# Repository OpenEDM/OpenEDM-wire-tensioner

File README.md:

# OpenEDM-wire-tensioner

This repository contains the design of the **Wire Tensioning Mechanism**, in particular, hardware design and firmware. Note that this design is a work in progress, it is not complete, and may contain errors.

Currently, the electronic hardware is assembled from heavily customized standard modules, as shown in the image below. An integrated hardware design is available in the [Hardware](https://github.com/OpenEDM/OpenEDM-wire-tensioner/tree/main/Hardware) directory, but it is still in the early stages of development.

The mechanical design of the wire tensioner is available as a part of the [OpenEDM-wire-machine design](https://github.com/OpenEDM/OpenEDM-wire-machine).

## Main design requirements

The wire tensioning mechanism must fulfill two main tasks:

1. Ensure that the wire in the cutting zone is fed according to the speed setpoint set by the user.
2. Ensure that the wire in the cutting zone is tensioned according to the tension setpoint set by the user.

## Operation principle

First, this is how the wire runs. On the right side (not shown in the photo) is the wire source; for example, a spool with new wire. On the left side (also not shown in the photo) is the location where the used wire is directed. This could be a spool for collecting the used wire, or a mechanism that cuts the wire into small pieces for convenient disposal:

Next, let's take a look at the wire tensioner's main components:

The wire enters the system through the **input wire feeder** (1). Then it passes around several passive pulleys. Next, the wire goes through the **wire guides** (6, 5). The **wire contacts** (7, 4), located near the wire guides, supply electricity to the wire. After that, the wire wraps around the last passive pulley, which is a part of the **load cell assembly** (10). Finally, the wire exits the system through the **output wire feeder** (8). All components are mounted on a frame, which consists of an **aluminum part** (2) and a **plastic part** (3). The system is controlled by an **electronic control unit** (9).

The system operates in such a way that the output feeder pulls the wire, while the input feeder, when necessary, slows the wire's movement by acting as a brake. The operation of the motors depends on the setpoints for speed and tension, as well as on the feedback signal from the load cell. More details are provided below.

There is an important design constraint for the input feeder: it must not deform the wire in any way, meaning it must not alter the shape of wire's cross-section. This constraint does not apply to the output feeder.

### Input wire feeder

To understand how this feeder works, let's look at how the wire is loaded into it. The wire enters the feeder through a PTFE tube connected to the **input fitting** (1.2). About one meter of wire should be pulled out from the tube, then placed into the groove of the **input latch** (1.1), and the latch should be closed. Next, the wire should be wrapped 4–5 times clockwise around the **pulley** (1.3). It doesn't matter if the loops are placed randomly; during operation, the feeder will self-correct their position. After that, without releasing the tension on the wire, the wire should be placed into the groove of the **output latch** (1.4) and the latch should be closed.

Some important points:
1. This feeder operates based on the [capstan effect](https://en.wikipedia.org/wiki/Capstan_equation).
1. For the feeder to operate correctly, the motor must rotate only clockwise, and there must always be some tension in the wire after the output latch.
1. Regarding the latches: the input and output latches are structurally identical. The input latch is shown in the closed position in the picture above, while the output latch is shown open. A closed latch significantly hinders the wire from passing through but does not block its movement completely.

### Output wire feeder

In this feeder, the main components are the pulleys, between which the wire is clamped. **Active puley** (8.6) is mounted directly on the motor shaft. **Passive puley** (8.7) is mounted on the **lever** (8.1) which rotates around the **axis** (8.3). Both pulleys have toothed rims that provide a kinematic connection between them. A **spring** (8.4), which presses against the **stop** (8.5), applies force to the lever, pushing the pulleys together and ensuring that the wire clamped between them cannot slip.

Again, let’s look at how the wire is loaded into this feeder. First, the lever (8.1) must be pressed to create a gap between pulleys (8.6) and (8.7). Then, the wire should be inserted into the hole marked with a red arrow. After that, the wire should pass between the pulleys and exit through the **output fitting** (8.2). Finally, the lever should be released so that the wire is clamped between the pulleys.

The main feature of this design is the construction of the pulleys. The pulleys must meet the following key requirements:

1. The surface that comes into contact with the wire must be hard enough so that the wire does not leave marks or cause deformation.
1. The pulleys must have an integrated toothed rim.

If the pulleys were made entirely of metal, manufacturing them would be a complex and costly task. However, a workaround was found that significantly simplifies the situation and reduces the cost. Each pulley is an assembly of three components:

1. An **outer bushing** (8.6.3) and an **inner bushing** (8.6.1). These bushings must be made of steel. However, due to their simple geometry, they can easily be sourced as off-the-shelf parts.
1. An **intermediate bushing** (8.6.2) with an integrated toothed rim. This bushing can simply be 3D-printed from a sufficiently strong plastic, such as ABS.

All three bushings -- outer, inner, and intermediate -- are press-fitted into one another. Of course, the dimensions of the plastic bushing must be chosen carefully to ensure a tight fit. This solution has been tested and has proven to work reliably in practice.

Another interesting aspect is the placement of the spring. It is easy to notice that the design of this feeder resembles that of a standard 3D printer extruder, for example, like [this one](https://youtu.be/zdTyMRBLIl4?t=35). However, in a typical 3D printer extruder, the spring is usually located inside, between the levers. In this design, the spring is placed on the outside.

The reason for this is that, for the feeder to work reliably, the pulleys axes must remain parallel, even when the spring applies significant pressure to the moving lever. Experiments have shown that the design with an externally mounted spring performs better in this regard.

### Load cell assembly

There is nothing particularly special about this part of the design. The **load cell** (10.2) is mounted on the wire tensioner frame using a **plastic holder** (10.1). The **passive pulley** (10.3) is attached to the load cell via another **plastic holder** (10.4).

The only noteworthy detail here is that the cable connecting the load cell to the electronic control unit is shielded, and the shield is electrically connected to the load cell beam. Often, the load cell beam is made of anodized aluminum, which prevents proper electrical contact; therefore, the anodized layer must be locally removed before connecting the cable shield to the beam.

### Control system operation algorithm

The current firmware version is located in the [corresponding folder](https://github.com/OpenEDM/OpenEDM-wire-tensioner/tree/main/Firmware). Below is a brief description of how it works:

Immediately after power is applied, the device performs a tare operation on the load cell. At this point, it is assumed that the wire is already loaded into the system. The input motor does not rotate. The output motor rotates in reverse to reduce the wire tension in the system. This reverse motion continues until the reading from the load cell stops changing. After that, the load cell is tared, and the device enters normal operation mode.

During normal operation, the following occurs:

1. The speed of the input motor depends only on the wire feed rate setpoint.
1. The speed of the output motor is controlled by a PID regulator, which receives the tension error as input -- that is, the difference between the actual tension (measured by the load cell) and the target tension set by the user.
1. The motors operate only if the output of the load cell exceeds a threshold value (by default, 500 grams). If the load cell reads below this threshold, it most likely indicates a broken wire, and the motors remain stopped.

## Electronic control unit

The electronic control unit is currently assembled from the following components:

1. NUCLEO-L432KC STM32 devboard.
1. (2x) TMC2209 stepper motor driver. The microstepping should be set to 1/16. The current should be set according to the motors.
1. SparkFun HX711 load cell amplifier. Should be modified according to the info below.

Here is the SparkFun HX711 schematic:

The following changes should be introdiced:

1. C1 should be replaced with 6.8u. The will change the LPF (C1, R3, R4) cutoff frequency to ~117Hz.
1. SJ2 should be opened so the data rate is 80SPS.

In addition to that, the shield of the load cell cable should be connected to JP4.1. These measures -- modifying the board and connecting the cable shield -- are necessary to reduce the influence of electromagnetic noise generated by the EDM on the load cell readings.

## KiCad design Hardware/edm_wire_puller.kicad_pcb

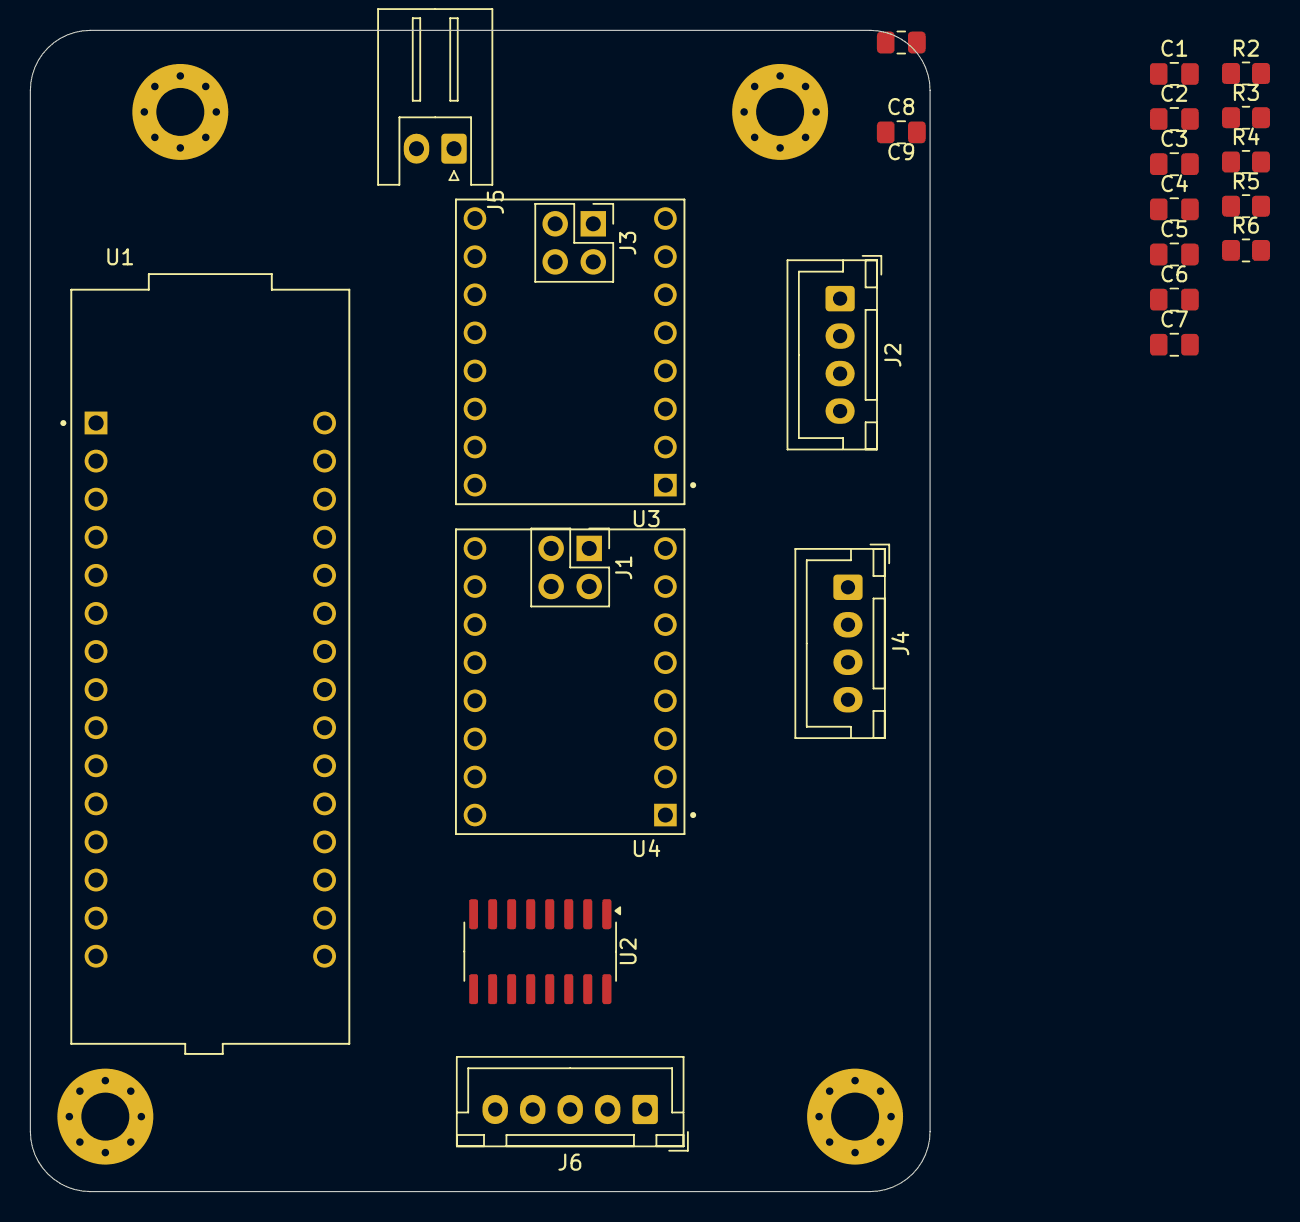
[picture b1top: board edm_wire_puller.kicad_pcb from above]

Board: 2 copper layers, 60.0 x 77.4 mm, 28 parts (0 on the bottom side), 24 nets, no tracks yet.

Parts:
C1, C2, C4, C6: 0.1u; C_0805_2012Metric_Pad1.18x1.45mm_HandSolder
C3: 6.8u; C_0805_2012Metric_Pad1.18x1.45mm_HandSolder
C5, C7: 10u; C_0805_2012Metric_Pad1.18x1.45mm_HandSolder
C8, C9: 1u; C_0805_2012Metric_Pad1.18x1.45mm_HandSolder
H1, H2, H3, H4: MountingHole_Pad; MountingHole_3.2mm_M3_Pad_Via
J1, J3: Conn_02x02_Top_Bottom; PinHeader_2x02_P2.54mm_Vertical
J2, J4: Conn_01x04; JST_XH_B4B-XH-A_1x04_P2.50mm_Vertical
J5: Conn_01x02; JST_XH_S2B-XH-A_1x02_P2.50mm_Horizontal
J6: Conn_01x05; JST_XH_B5B-XH-A_1x05_P2.50mm_Vertical
R2: 20k; R_0805_2012Metric_Pad1.20x1.40mm_HandSolder
R3: 8.2k; R_0805_2012Metric_Pad1.20x1.40mm_HandSolder
R4, R5: 100; R_0805_2012Metric_Pad1.20x1.40mm_HandSolder
R6: 10k; R_0805_2012Metric_Pad1.20x1.40mm_HandSolder
U1: NUCLEO-L412KB; MODULE_NUCLEO-L412KB
U2: HX711; SOP-16_3.9x9.9mm_P1.27mm
U3, U4: TMC2209; MODULE_TMC2209

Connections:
+5V: C1.1, C6.1, C7.1, J1.1, J1.2, J3.1, J3.2, R6.2, U2.1 (VSUP), U2.16 (DVDD), U3.2 (VIO), U4.2 (VIO)
+12V: J5.1, U3.8 (VM), U4.8 (VM)
A+: J6.4, R5.1
A-: J6.3, R4.2
E+: C4.2, C5.2, J6.1
GND: C1.2, C2.2, C4.1, C5.1, C6.2, C7.2, C8.2, C9.2, J5.2, J6.2, J6.5, R3.2, U1.CN4_2 (GND), U2.5 (AGND), U2.9 (INB-), U2.10 (INB+), U2.14 (XI), U3.1 (GND), U3.7 (GND), U4.1 (GND), U4.7 (GND)
M1_1A: J2.3, U3.4 (M1A)
M1_1B: J2.4, U3.3 (M1B)
M1_2A: J2.2, U3.5 (M2A)
M1_2B: J2.1, U3.6 (M2B)
M2_1A: J4.3, U4.4 (M1A)
M2_1B: J4.4, U4.3 (M1B)
M2_2A: J4.2, U4.5 (M2A)
M2_2B: J4.1, U4.6 (M2B)
unnamed: J1.3, U4.15 (MS1)
unnamed: J1.4, U4.14 (MS2)
unnamed: J3.3, U3.15 (MS1)
unnamed: J3.4, U3.14 (MS2)
unnamed: R6.1, U2.15 (RATE)
unnamed: R2.2, U2.3 (AVDD)
unnamed: C3.1, C8.1, C9.1, R5.2, U2.8 (INA+)
unnamed: C3.2, R4.1, U2.7 (INA-)
unnamed: C2.1, U2.6 (VBG)
unnamed: R2.1, R3.1, U2.4 (VFB)
